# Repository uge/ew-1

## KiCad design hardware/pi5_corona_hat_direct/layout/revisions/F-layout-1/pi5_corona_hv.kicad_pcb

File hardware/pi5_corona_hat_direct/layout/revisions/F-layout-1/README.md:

# Initial four-layer PCB placement

Open `../pi5_corona_hv.kicad_pro` and its PCB editor. The board is saved in KiCad 10 format. All 152 schematic footprints, net assignments, procurement fields and native schematic paths are imported. C63 and R64 remain DNP. Seven board-only mounting holes are added.

The main carrier is **340 × 180 mm**. The optical daughterboard is **30 × 20 mm**, connected by a **12 × 5 mm** break-off neck, for an overall **340 × 205 mm** envelope. These dimensions are an initial accommodation of the large through-hole multiplier parts and linear resistor strings, subject to enclosure and clearance review.

The upper-left 65 × 56 mm reference envelope contains the Pi interface. Four mounting holes use a 58 × 49 mm pitch. J2 is on B.Cu to mate with the Pi header: pad 1 at (58.37, 54.77), pad 2 at (58.37, 52.23), and pad 40 at (106.63, 52.23) mm. The mounting-hole drill is nominally 2.7 mm. Review mechanical tolerances and the Pi 5 cooler, cables and enclosure. This extended carrier is not a standard HAT outline or a claim of HAT certification. Mechanical reference: https://github.com/raspberrypi/hats/blob/master/hat-board-mechanical.pdf.

| Layer | Intended use |
|---|---|
| F.Cu | Components, short critical connections and HV routing |
| In1.Cu | Filled logic GND plane limited to the low-voltage area |
| In2.Cu | Reserved for local low-voltage power distribution |
| B.Cu | Pi socket and additional signal routing |

Nominal board thickness is 1.6 mm. Manufacturer dielectric thicknesses and copper weights remain to be selected. Internal-layer rule areas prohibit tracks, vias and fills under the transformer and HV area, starting at x = 122 mm. Through-hole annuli are permitted. GND is not poured beneath the HV ladder, ballast or divider. HV_RETURN remains a separate schematic net. These restrictions do not establish a verified creepage or voltage rating.

USB-C, PD negotiation, the eFuse and bulk capacitance form a distinct placement group. Bridge decoupling and recirculation clamps are near U2, and T1 bridges toward the multiplier. Six multiplier columns have paired capacitors, diodes and three-resistor bleeders. The ballast and divider are linear strings; the divider progresses back toward U4. U8, J51, C80 and C81 are on the optical mini-board; J50 is on the main board. Only GND, 3V3, SDA and SCL may eventually cross its break-off neck. Neck traces and the mechanical cutting process are not yet implemented.

## Validation and remaining work

The final checks report **zero schematic parity issues**, matching net assignments for every schematic pin, and no courtyard overlaps. The initial routing pass has **285 unconnected-item reports**. One DRC warning documents the D3 instance's silkscreen adjustment: its silk was moved to F.Fab to avoid pad overlap, so it differs from the library copy. The DRC report is retained in `../exports/initial-pcb-drc.json`; validation is in `../exports/initial-pcb-validation.json`.

Before routing/release, resolve the existing J60 termination rating, relay supply/interlock review and transformer footprint verification. Replace the J60 placeholder with a rated termination and rework its local placement. Complete routing, establish HV clearance/creepage rules and any isolation slots, review leakage around the divider, and validate transformer/bridge thermal and current paths. Do not fabricate this placement study.

Review drawings: `../exports/initial-pcb-layout.pdf`, `.svg` and `.png`. No fabrication package or production pick-and-place file is emitted.

`create_initial_board.py` uses the KiCad 10 pcbnew PCB API and `schematic-connectivity.json`. It does not generate schematics. Re-running it overwrites the PCB with the initial placement and discards subsequent routing, so use it only deliberately. The connectivity snapshot corresponds to schematic revision F and must be refreshed after schematic changes.

## DNP Raspberry Pi 5 mechanical model

**MP1** is a locked, padless board-only footprint, explicitly DNP and excluded from BOM and placement files. It uses the official Raspberry Pi 5 STEP model from [Raspberry Pi's product portal](https://pip.raspberrypi.com/categories/892-raspberry-pi-5), stored locally with the supplied MIT license in `ionic_thrust_hv.3dshapes`. It is not an electrically connected or assembled HAT component. The footprint is on F.Cu solely to retain the native model orientation; its model is translated beneath the carrier.

The native model's PCB spans x = 0–85 and y = 0–56 mm. Its upper PCB face is at z = 1.306 mm. MP1's board anchor is (50,106) mm, with model scale 1, rotation 0 and offset (0,0,-14.906) mm. This places the Pi PCB upper face **12 mm below the carrier underside**, assuming the carrier's 1.6 mm thickness. This height is a fit-check assumption, not a validated connector mating specification.

The official header pins are centered at y = 51.23 and 53.77 mm in native CAD coordinates. Comparing these with the PCB exposed a 1.27 mm GPIO row offset; J2 was moved by -1.27 mm in board Y. All 40 pin coordinates now match the model's grid, and the four Pi mounting locations align. The existing schematic connections and connector selection are preserved.

**The extended carrier collides with the tall Pi connectors at the assumed 12 mm spacing.** The model reaches z = 17.526 mm, or 16.220 mm above the Pi PCB upper face. Geometric clearance requires more than 16.22 mm standoff spacing plus a mechanical margin, or carrier cut-outs. A taller stack also requires an appropriate GPIO extender; do not assume J2 alone provides that height. A cooler, cables and enclosure are not included in this model and need separate checks.

In KiCad's 3D Viewer, enable **Show DNP footprints** to display MP1. STEP export includes it unless `--no-dnp` is passed. The saved PCB remains DNP; the bottom-view preview was rendered from a temporary display copy with MP1 visible. See `../exports/pi5-mechanical-bottom.png` and `../exports/pi5-mechanical-validation.json`. `add_pi5_mechanical.py` updates only MP1 and the corrected J2 XY location without rebuilding the PCB or discarding routing. The initial-board script also restores MP1 when deliberately rebuilding.

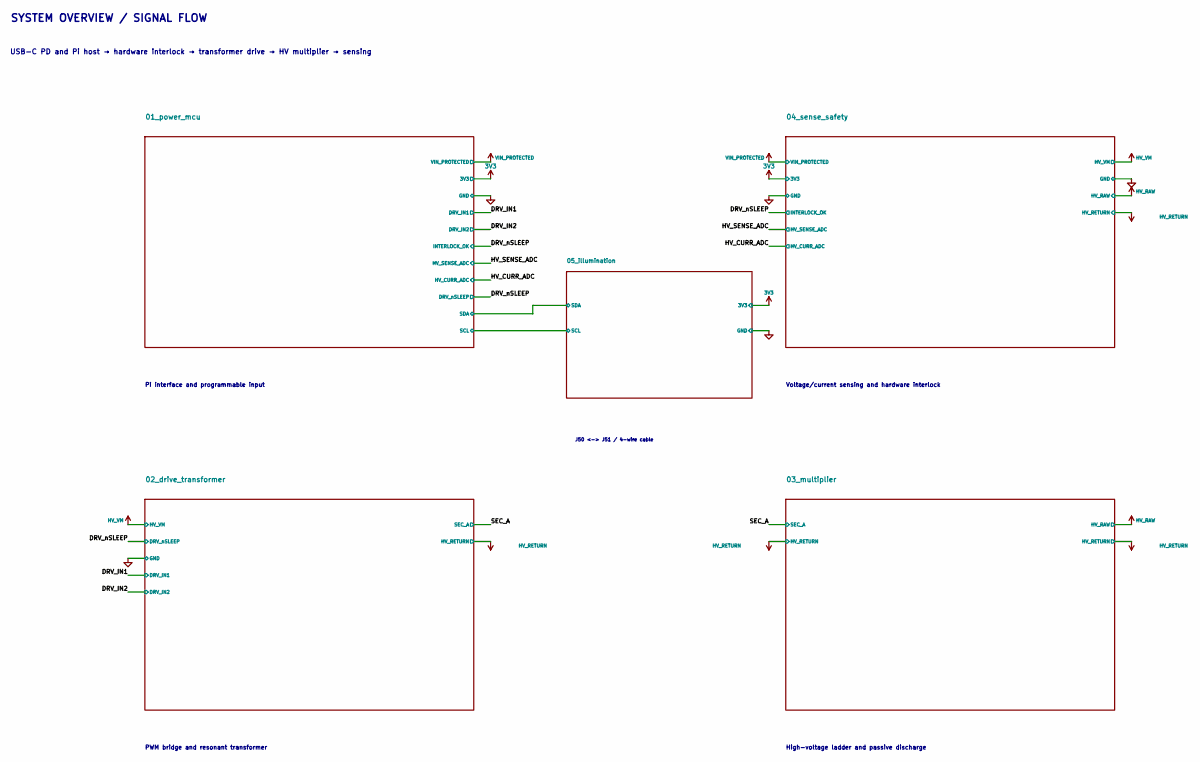
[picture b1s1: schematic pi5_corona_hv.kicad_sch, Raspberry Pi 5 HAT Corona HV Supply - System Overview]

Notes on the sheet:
SYSTEM OVERVIEW / SIGNAL FLOW
USB-C PD and Pi host → hardware interlock → transformer drive → HV multiplier → sensing
Pi interface and programmable input
Voltage/current sensing and hardware interlock
PWM bridge and resonant transformer
High-voltage ladder and passive discharge
J50 <-> J51 / 4-wire cable

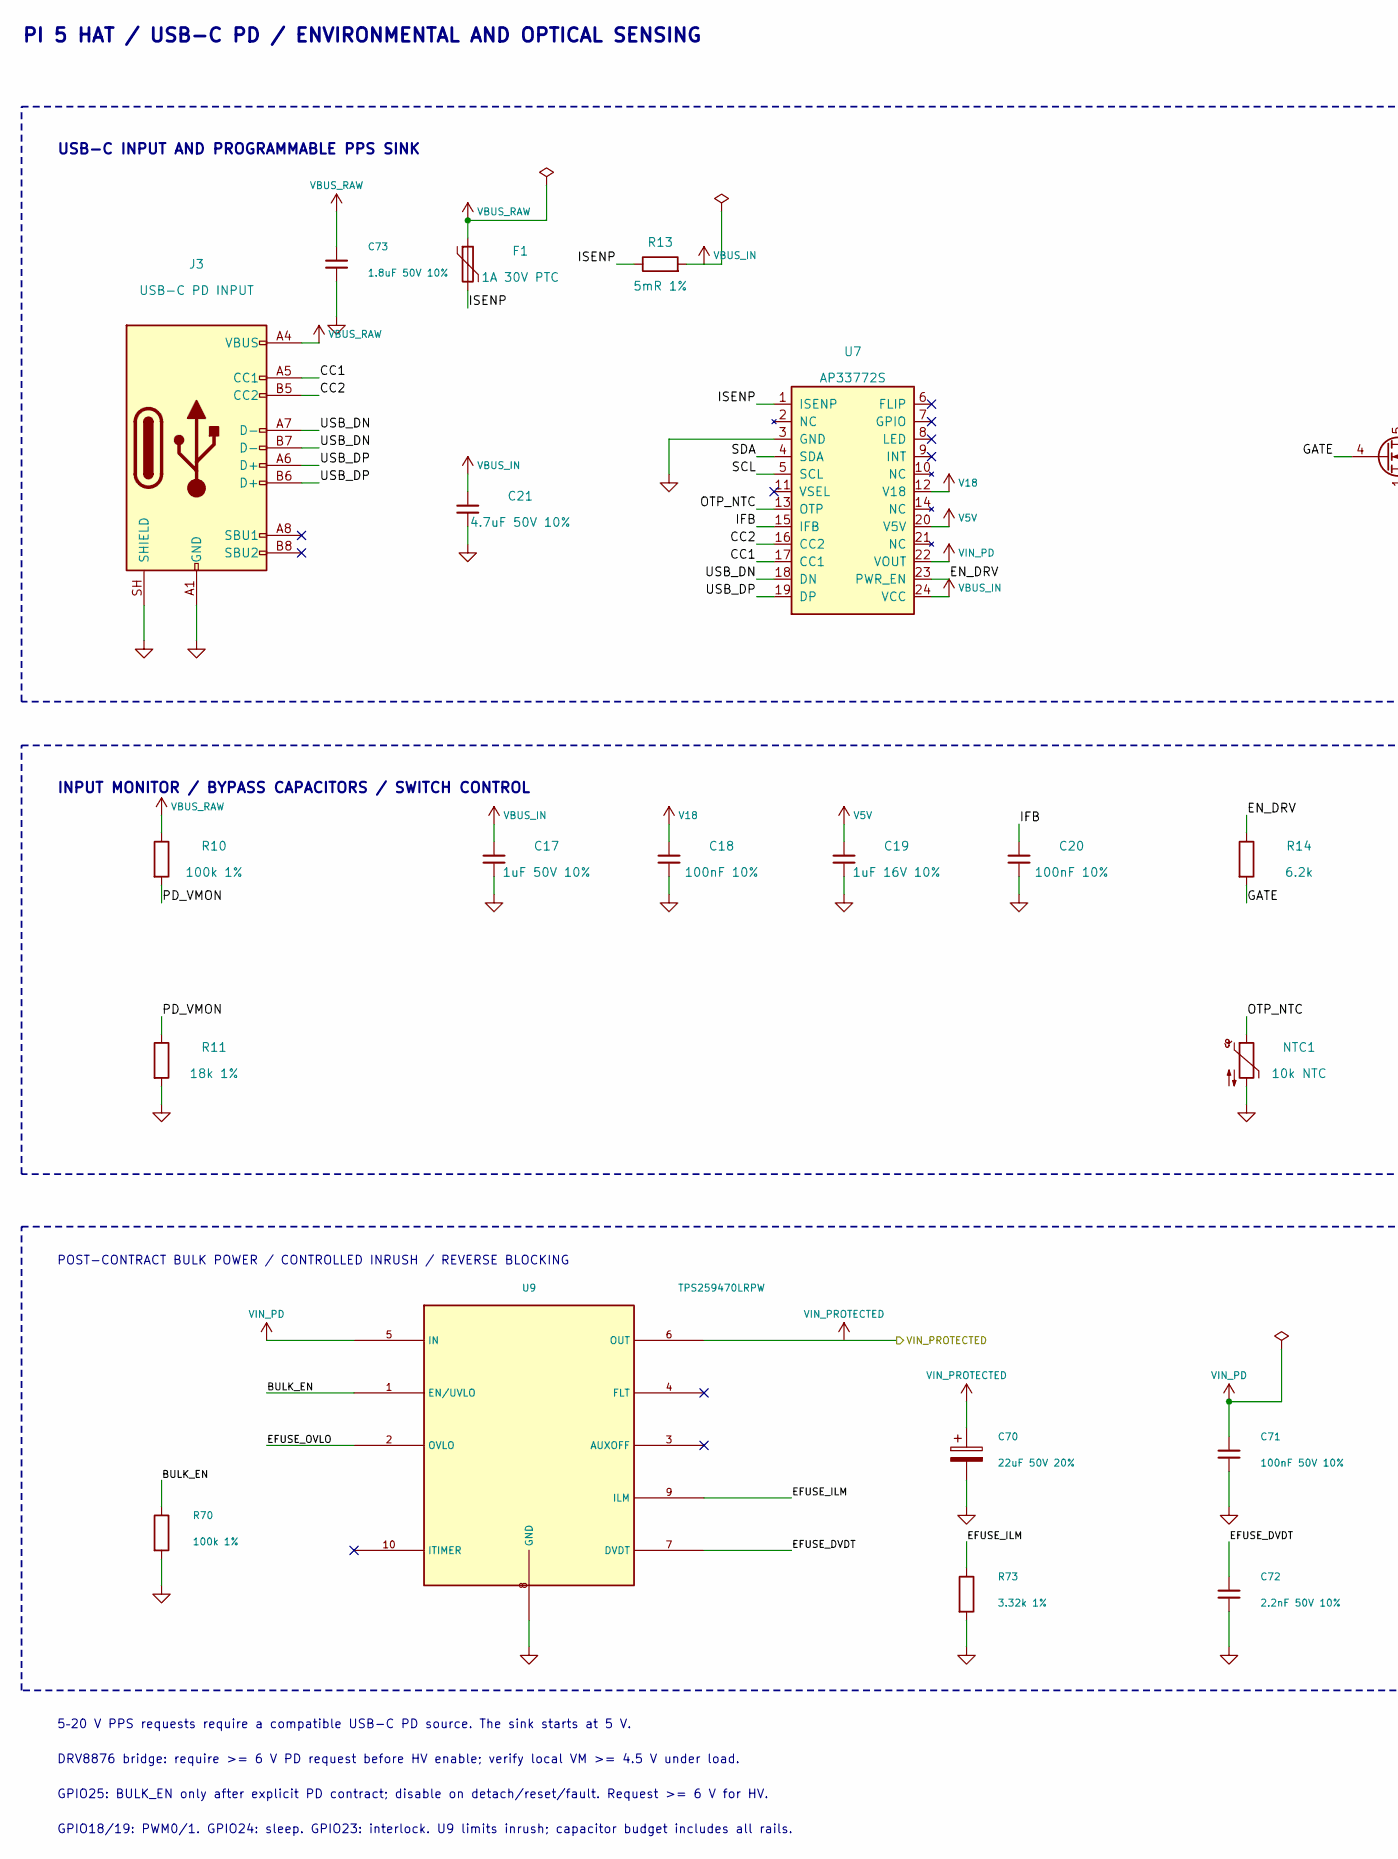
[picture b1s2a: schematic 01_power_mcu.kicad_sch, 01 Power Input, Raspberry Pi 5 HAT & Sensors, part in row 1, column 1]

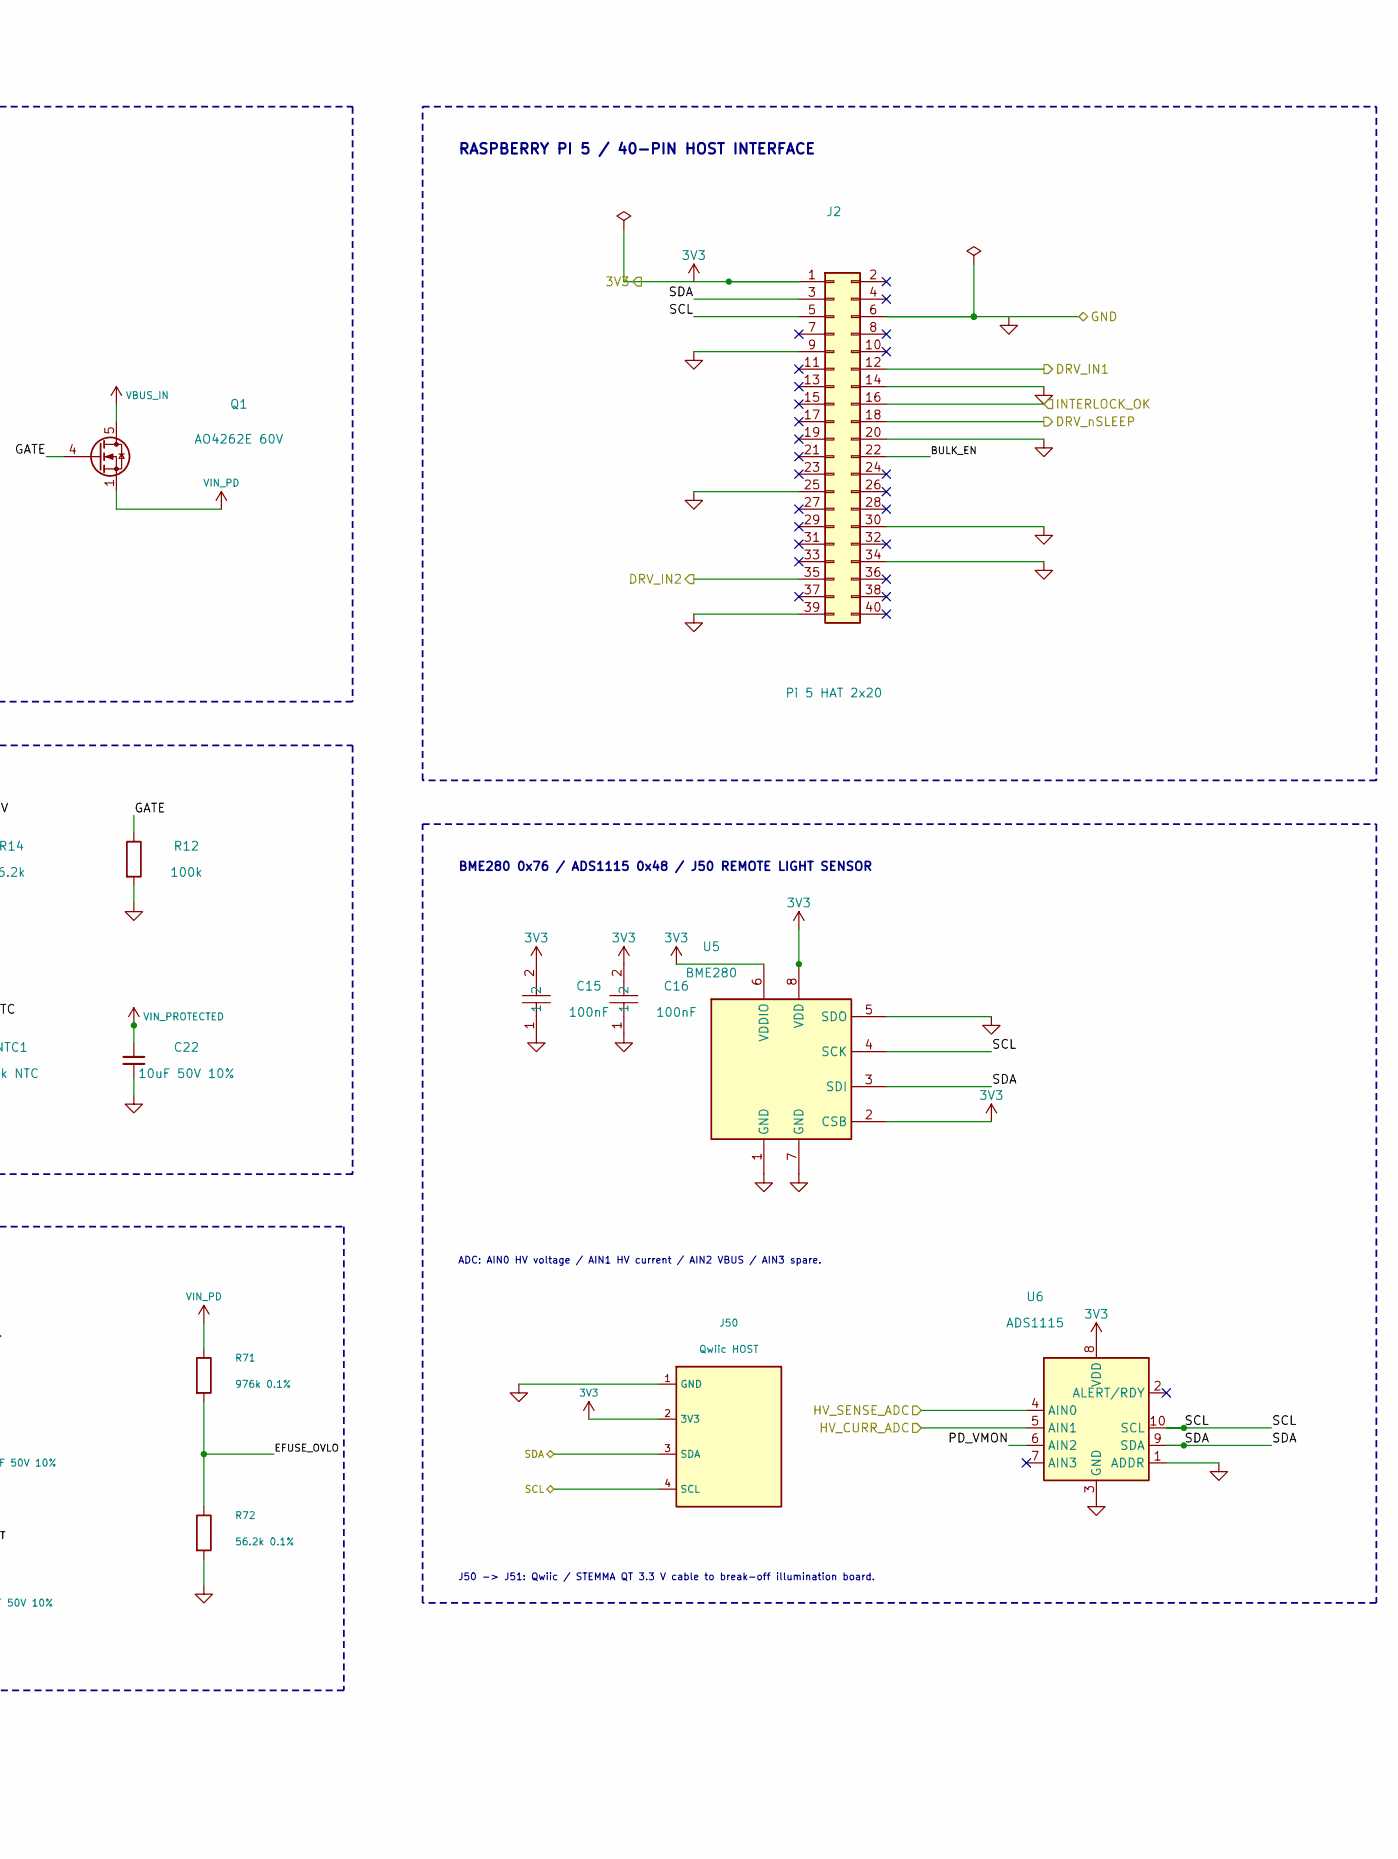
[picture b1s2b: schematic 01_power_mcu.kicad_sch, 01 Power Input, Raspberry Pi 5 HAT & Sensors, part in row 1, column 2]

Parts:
C15, C16: 100nF; C0603; MPN CC0603KRX7R9BB104; LCSC C14663
C17: 1uF 50V 10%; C_0603_1608Metric; MPN CL10B105KB8NQNC; LCSC C5199872
C18, C20: 100nF 10%; C_0603_1608Metric; MPN CC0603KRX7R9BB104; LCSC C14663
C19: 1uF 16V 10%; C_0603_1608Metric; MPN CL10B105KB8NQNC; LCSC C5199872
C21: 4.7uF 50V 10%; C_1210_3225Metric; MPN GCM32ER71H475KA55L; LCSC C126618
C22: 10uF 50V 10%; C_1210_3225Metric; MPN UMK325AB7106KMHP; LCSC C386166
C70: 22uF 50V 20%; CP_Radial_D5.0mm_P2.00mm; MPN 50YXF22MEFC5X11; LCSC C88755
C71: 100nF 50V 10%; C_0603_1608Metric; MPN CC0603KRX7R9BB104; LCSC C14663
C72: 2.2nF 50V 10%; C_0603_1608Metric; MPN 0603B222K500NT; LCSC C1604
C73: 1.8uF 50V 10%; C_2220_5750Metric; MPN C2220C185J5RAC7800; LCSC C3900748
F1: 1A 30V PTC; Fuse_1206_3216Metric; MPN BSMD1206-100-30V; LCSC C5358568
J2: Pi 5 HAT 2x20; PinSocket_2x20_P2.54mm_Vertical; MPN 2.54-2*20; LCSC C2977589
J3: USB-C PD INPUT; USB_C_Receptacle_HCTL_HC-TYPE-C-16P-01A; MPN HC-TYPE-C-16P-01A; LCSC C2894897
J50: Qwiic HOST; JST_SH_SM04B-SRSS-TB_1x04-1MP_P1.00mm_Horizontal; MPN SM04B-SRSS-TB(LF)(SN); LCSC C160404
NTC1: 10k NTC; R_0603_1608Metric; MPN NCP18XH103F03RB; LCSC C13564
Q1: AO4262E 60V; SO-8_3.9x4.9mm_P1.27mm; MPN AO4262E; LCSC C431178
R10, R70: 100k 1%; R_0603_1608Metric; MPN 0603WAF1003T5E; LCSC C25803
R11: 18k 1%; R_0603_1608Metric; MPN 0603WAF1802T5E; LCSC C25810
R12: 100k; R_0603_1608Metric; MPN 0603WAF1003T5E; LCSC C25803
R13: 5mR 1%; R_2512_6332Metric; MPN RLP25FEGMR005; LCSC C393074
R14: 6.2k; R_0603_1608Metric; MPN 0603WAF6201T5E; LCSC C4260
R71: 976k 0.1%; R_0805_2012Metric; MPN RT0805BRD07976KL; LCSC C865713
R72: 56.2k 0.1%; R_0603_1608Metric; MPN RT0603BRD0756K2L; LCSC C705784
R73: 3.32k 1%; R_0603_1608Metric; MPN RT0603FRD073K32L; LCSC C863430
U5: BME280; Bosch_LGA-8_2.5x2.5mm_P0.65mm_ClockwisePinNumbering; MPN BME280; LCSC C92489
U6: ADS1115; TSSOP-10_3x3mm_P0.5mm; MPN ADS1115IDGSR; LCSC C37593
U7: AP33772S; QFN-24-1EP_4x4mm_P0.5mm_EP2.7x2.7mm; MPN AP33772SDKZ-13-FA01; LCSC C24374260
U9: TPS259470LRPW; Texas_RPW0010A_VQFN-HR-10_2x2mm; MPN TPS259470LRPWR; LCSC C3662793

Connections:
3V3: C15.2, C16.2, J2.1, J50.2 (3V3), U5.2 (CSB), U5.6 (VDDIO), U5.8 (VDD), U6.8 (VDD); also elsewhere on the board
/01_power_mcu/BULK_EN: J2.22, R70.1, U9.1 (EN/UVLO)
/01_power_mcu/CC1: J3.A5 (CC1), U7.17 (CC1)
/01_power_mcu/CC2: J3.B5 (CC2), U7.16 (CC2)
/01_power_mcu/EFUSE_DVDT: C72.1, U9.7 (DVDT)
/01_power_mcu/EFUSE_ILM: R73.1, U9.9 (ILM)
/01_power_mcu/EFUSE_OVLO: R71.2, R72.1, U9.2 (OVLO)
/01_power_mcu/EN_DRV: R14.1, U7.23 (PWR_EN)
/01_power_mcu/GATE: Q1.4 (G), R12.1, R14.2
/01_power_mcu/IFB: C20.1, U7.15 (IFB)
/01_power_mcu/ISENP: F1.2, R13.1, U7.1 (ISENP)
/01_power_mcu/OTP_NTC: NTC1.1, U7.13 (OTP)
/01_power_mcu/PD_VMON: R10.2, R11.1, U6.6 (AIN2)
/01_power_mcu/SCL: J2.5, J50.4 (SCL), U5.4 (SCK), U6.10 (SCL), U7.5 (SCL); also elsewhere on the board
/01_power_mcu/SDA: J2.3, J50.3 (SDA), U5.3 (SDI), U6.9 (SDA), U7.4 (SDA); also elsewhere on the board
/01_power_mcu/USB_DN: J3.A7 (D-), J3.B7 (D-), U7.18 (DN)
/01_power_mcu/USB_DP: J3.A6 (D+), J3.B6 (D+), U7.19 (DP)
/01_power_mcu/V5V: C19.1, U7.20 (V5V)
/01_power_mcu/V18: C18.1, U7.12 (V18)
/01_power_mcu/VBUS_IN: C17.1, C21.1, Q1.5 (D), Q1.6 (D), Q1.7 (D), Q1.8 (D), R13.2, U7.24 (VCC)
/01_power_mcu/VBUS_RAW: C73.1, F1.1, J3.A4 (VBUS), J3.A9 (VBUS), J3.B4 (VBUS), J3.B9 (VBUS), R10.1
/01_power_mcu/VIN_PD: C71.1, Q1.1 (S), Q1.2 (S), Q1.3 (S), R71.1, U7.22 (VOUT), U9.5 (IN)
/DRV_IN1: J2.12; also elsewhere on the board
/DRV_IN2: J2.35; also elsewhere on the board
/DRV_nSLEEP: J2.16, J2.18; also elsewhere on the board
/HV_CURR_ADC: U6.5 (AIN1); also elsewhere on the board
/HV_SENSE_ADC: U6.4 (AIN0); also elsewhere on the board
/VIN_PROTECTED: C22.1, C70.1, U9.6 (OUT); also elsewhere on the board
GND: C15.1, C16.1, C17.2, C18.2, C19.2, C20.2, C21.2, C22.2, C70.2, C71.2, C72.2, C73.2, J2.6, J2.9, J2.14, J2.20, J2.25, J2.30, J2.34, J2.39, J3.A1 (GND), J3.A12 (GND), J3.B1 (GND), J3.B12 (GND), J3.SH (SHIELD), J50.1 (GND), NTC1.2, R11.2, R12.2, R70.2, R72.2, R73.2, U5.1 (GND), U5.5 (SDO), U5.7 (GND), U6.1 (ADDR), U6.3 (GND), U7.3 (GND), U7.25 (GND), U9.8 (GND); also elsewhere on the board

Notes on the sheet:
PI 5 HAT / USB-C PD / ENVIRONMENTAL AND OPTICAL SENSING
USB-C INPUT AND PROGRAMMABLE PPS SINK
INPUT MONITOR / BYPASS CAPACITORS / SWITCH CONTROL
RASPBERRY PI 5 / 40-PIN HOST INTERFACE
BME280 0x76 / ADS1115 0x48 / J50 REMOTE LIGHT SENSOR
5–20 V PPS requests require a compatible USB-C PD source. The sink starts at 5 V.
DRV8876 bridge: require >= 6 V PD request before HV enable; verify local VM >= 4.5 V under load.
GPIO25: BULK_EN only after explicit PD contract; disable on detach/reset/fault. Request >= 6 V for HV.
GPIO18/19: PWM0/1. GPIO24: sleep. GPIO23: interlock. U9 limits inrush; capacitor budget includes all rails.
ADC: AIN0 HV voltage / AIN1 HV current / AIN2 VBUS / AIN3 spare.
J50 -> J51: Qwiic / STEMMA QT 3.3 V cable to break-off illumination board.
POST-CONTRACT BULK POWER / CONTROLLED INRUSH / REVERSE BLOCKING

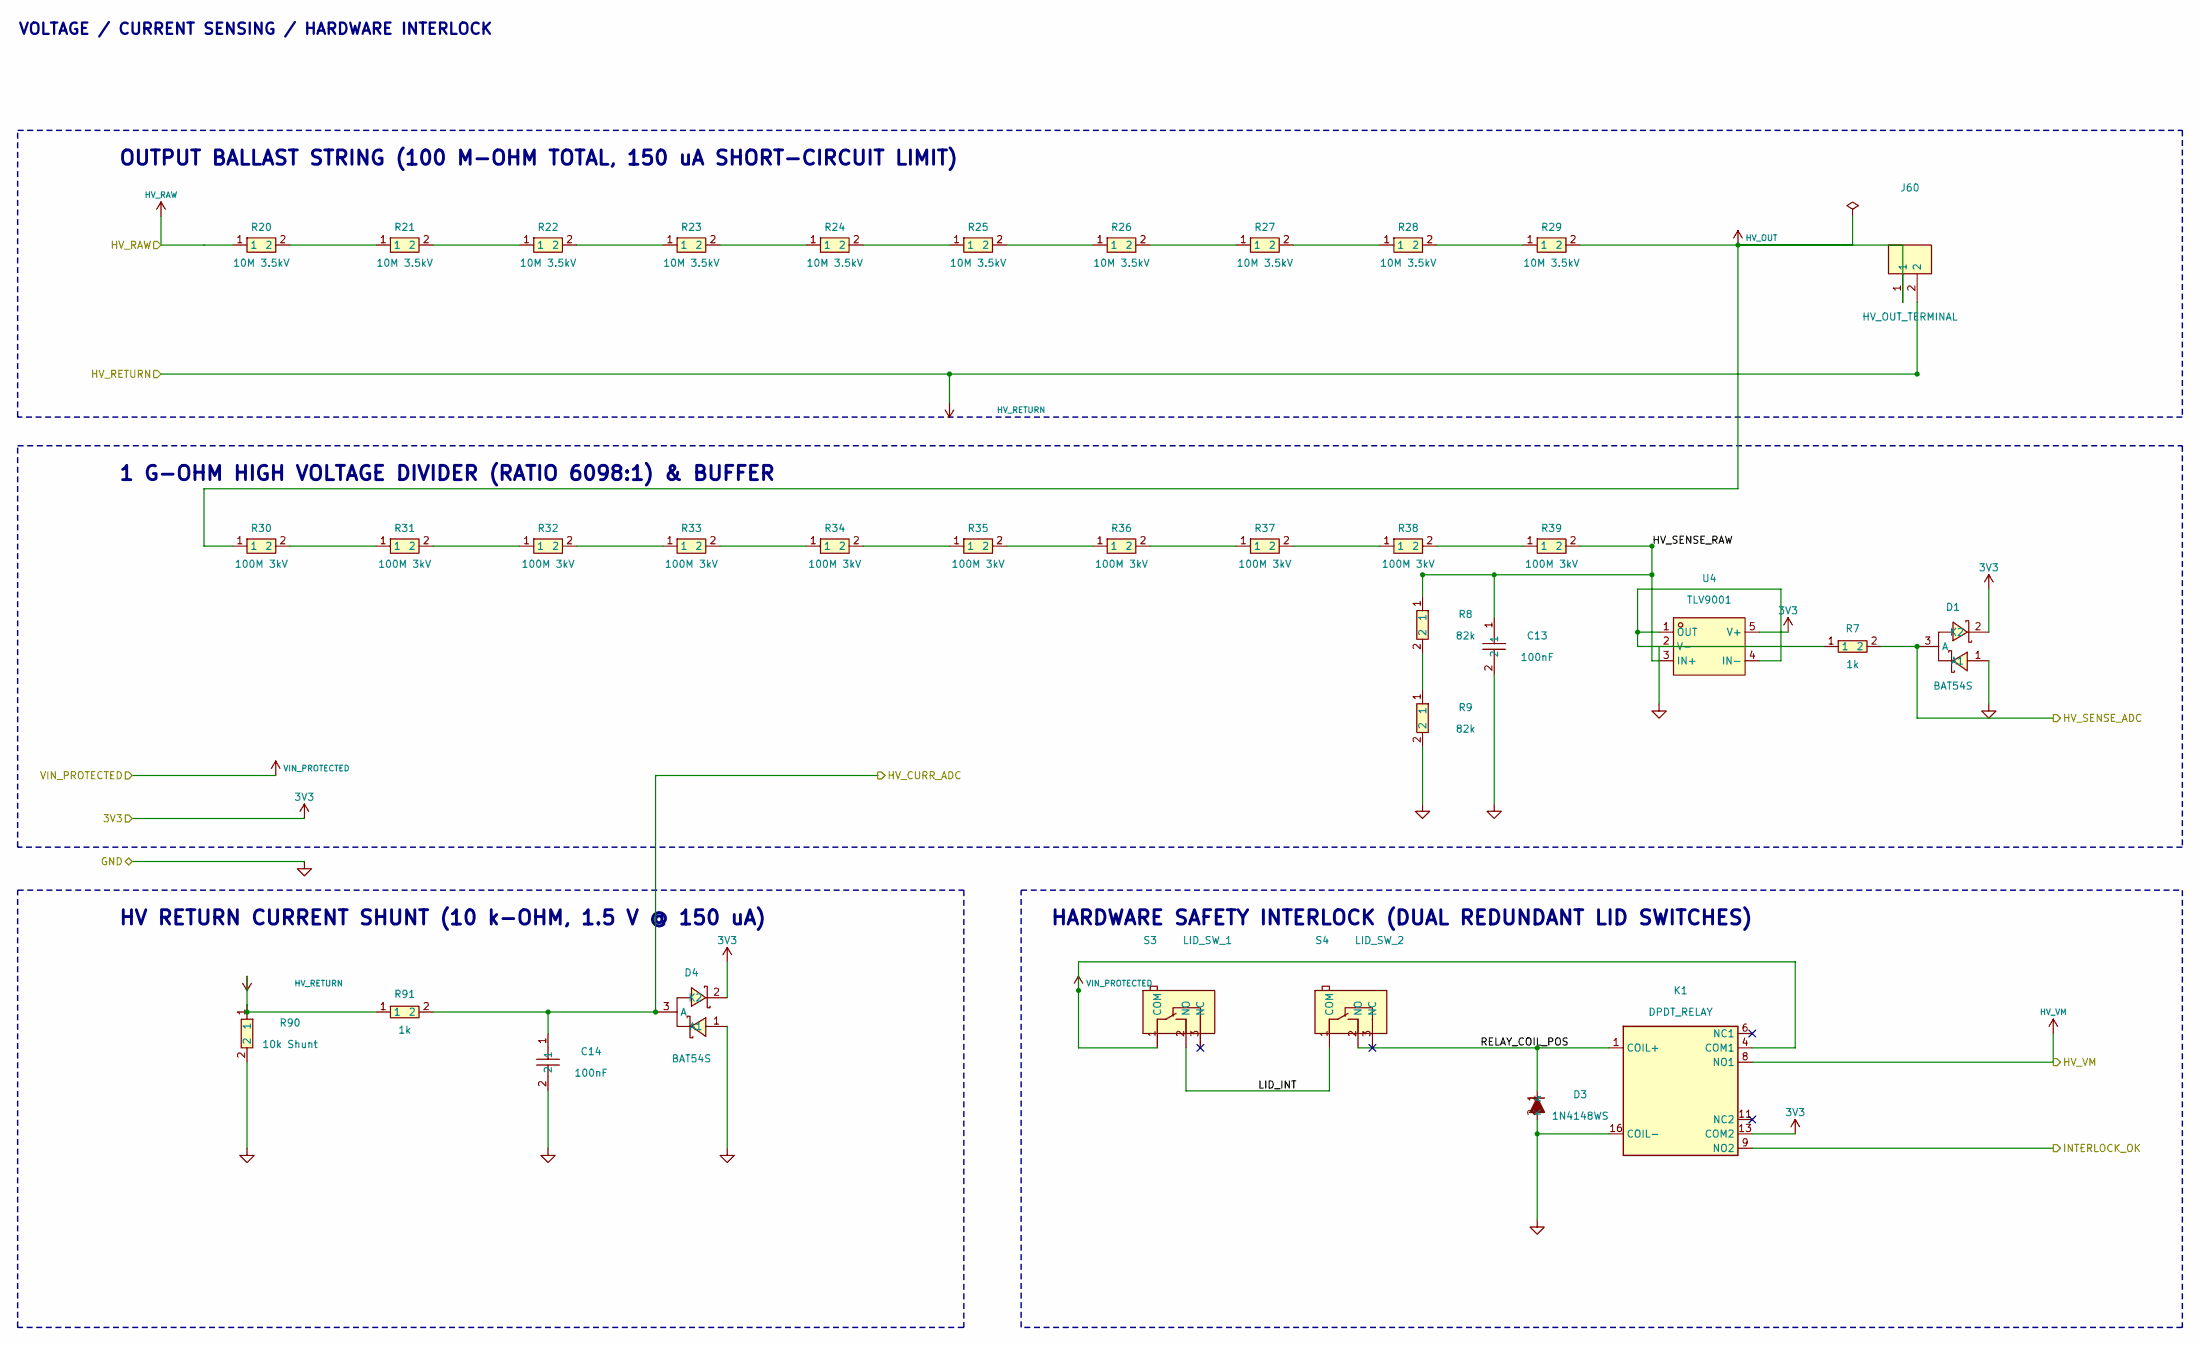
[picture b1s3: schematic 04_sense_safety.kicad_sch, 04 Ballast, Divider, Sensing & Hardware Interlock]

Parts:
C13, C14: 100nF; C0603; MPN CC0603KRX7R9BB104; LCSC Part C14663
D1, D4: BAT54S; SOT-23-3_L2.9-W1.3-P1.90-LS2.4-BR; MPN BAT54S; LCSC Part C83935
D3: 1N4148WS; D_SOD-323; MPN 1N4148WS; LCSC Part C2128
J60: HV_OUT_TERMINAL; CONN-TH_2P-P5.00_WJ500V-5.08-2P; JLCPCB Library Unknown
K1: DPDT_RELAY; Relay_DPDT_N4078; MPN N4078-2C-DC12V-0.2W; LCSC Part C52195125
R7, R91: 1k; R0603; MPN 0603WAF1001T5E; LCSC Part C21190
R8, R9: 82k; R0603; MPN 0603WAF8202T5E; LCSC Part C23254
R20, R21, R22, R23, R24, R25, R26, R27, R28, R29: 10M 3.5kV; RES-TH_BD3.5-L9.5-P13.50-D0.6; MPN MGR0W2J0106A10; LCSC Part C51904770
R30, R31, R32, R33, R34, R35, R36, R37, R38, R39: 100M 3kV; R_2512_6332Metric; MPN CHV2512-JW-107ELF; LCSC Part C2089706
R90: 10k Shunt; R0603; MPN 0603WAF1002T5E; LCSC Part C25804
S3: LID_SW_1; SW-TH_D2F-L; MPN D2F-L; LCSC Part C231337
S4: LID_SW_2; SW-TH_D2F-L; MPN D2F-L; LCSC Part C231337
U4: TLV9001; SOT-23-5_L3.0-W1.7-P0.95-LS2.8-BR; MPN TLV9001IDBVR; LCSC Part C398363

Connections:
3V3: D1.2 (K2), D4.2 (K2), K1.13 (COM2), U4.5 (V+); also elsewhere on the board
/04_sense_safety/HV_OUT: J60.1, R29.2, R30.1
/04_sense_safety/HV_SENSE_RAW: C13.1, R8.1, R39.2, U4.3 (IN+)
/04_sense_safety/LID_INT: S3.2 (NO), S4.1 (COM)
/04_sense_safety/RELAY_COIL_POS: D3.1 (K), K1.1 (COIL+), S4.2 (NO)
/DRV_nSLEEP: K1.9 (NO2); also elsewhere on the board
/HV_CURR_ADC: C14.1, D4.3 (A), R91.2; also elsewhere on the board
/HV_RAW: R20.1; also elsewhere on the board
/HV_RETURN: J60.2, R90.1, R91.1; also elsewhere on the board
/HV_SENSE_ADC: D1.3 (A), R7.2; also elsewhere on the board
/HV_VM: K1.8 (NO1); also elsewhere on the board
/VIN_PROTECTED: K1.4 (COM1), S3.1 (COM); also elsewhere on the board
GND: C13.2, C14.2, D1.1 (A1), D3.2 (A), D4.1 (A1), K1.16 (COIL-), R9.2, R90.2, U4.2 (V-); also elsewhere on the board
unnamed: R8.2, R9.1
unnamed: R20.2, R21.1
unnamed: R21.2, R22.1
unnamed: R22.2, R23.1
unnamed: R23.2, R24.1
unnamed: R24.2, R25.1
unnamed: R25.2, R26.1
unnamed: R26.2, R27.1
unnamed: R27.2, R28.1
unnamed: R28.2, R29.1
unnamed: R30.2, R31.1
unnamed: R31.2, R32.1
unnamed: R32.2, R33.1
unnamed: R33.2, R34.1
unnamed: R34.2, R35.1
unnamed: R35.2, R36.1
unnamed: R36.2, R37.1
unnamed: R37.2, R38.1
unnamed: R38.2, R39.1
unnamed: R7.1, U4.1 (OUT), U4.4 (IN-)

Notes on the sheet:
OUTPUT BALLAST STRING (100 M-OHM TOTAL, 150 uA SHORT-CIRCUIT LIMIT)
1 G-OHM HIGH VOLTAGE DIVIDER (RATIO 6098:1) & BUFFER
HV RETURN CURRENT SHUNT (10 k-OHM, 1.5 V @ 150 uA)
HARDWARE SAFETY INTERLOCK (DUAL REDUNDANT LID SWITCHES)
VOLTAGE / CURRENT SENSING / HARDWARE INTERLOCK

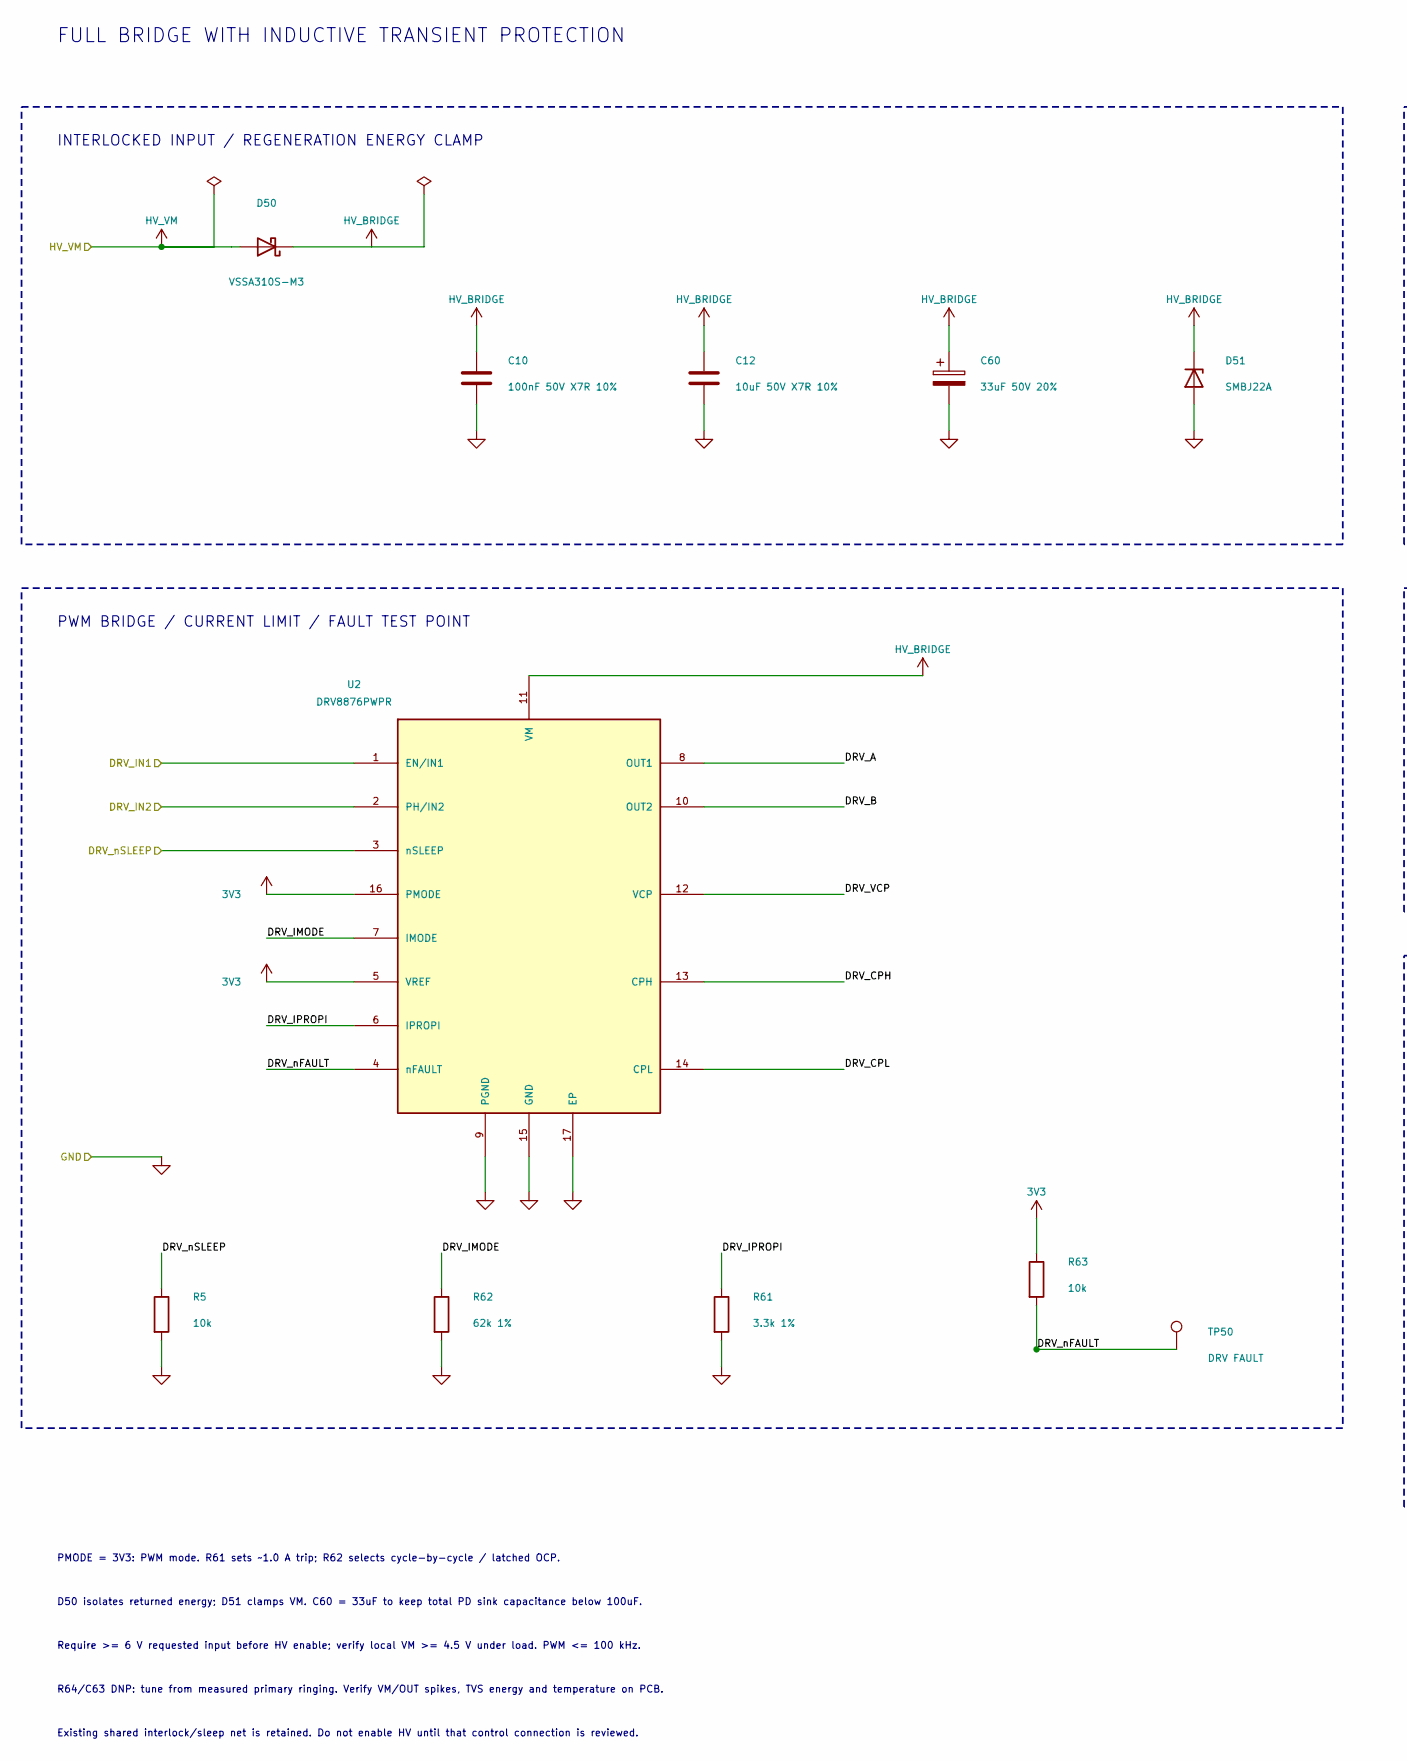
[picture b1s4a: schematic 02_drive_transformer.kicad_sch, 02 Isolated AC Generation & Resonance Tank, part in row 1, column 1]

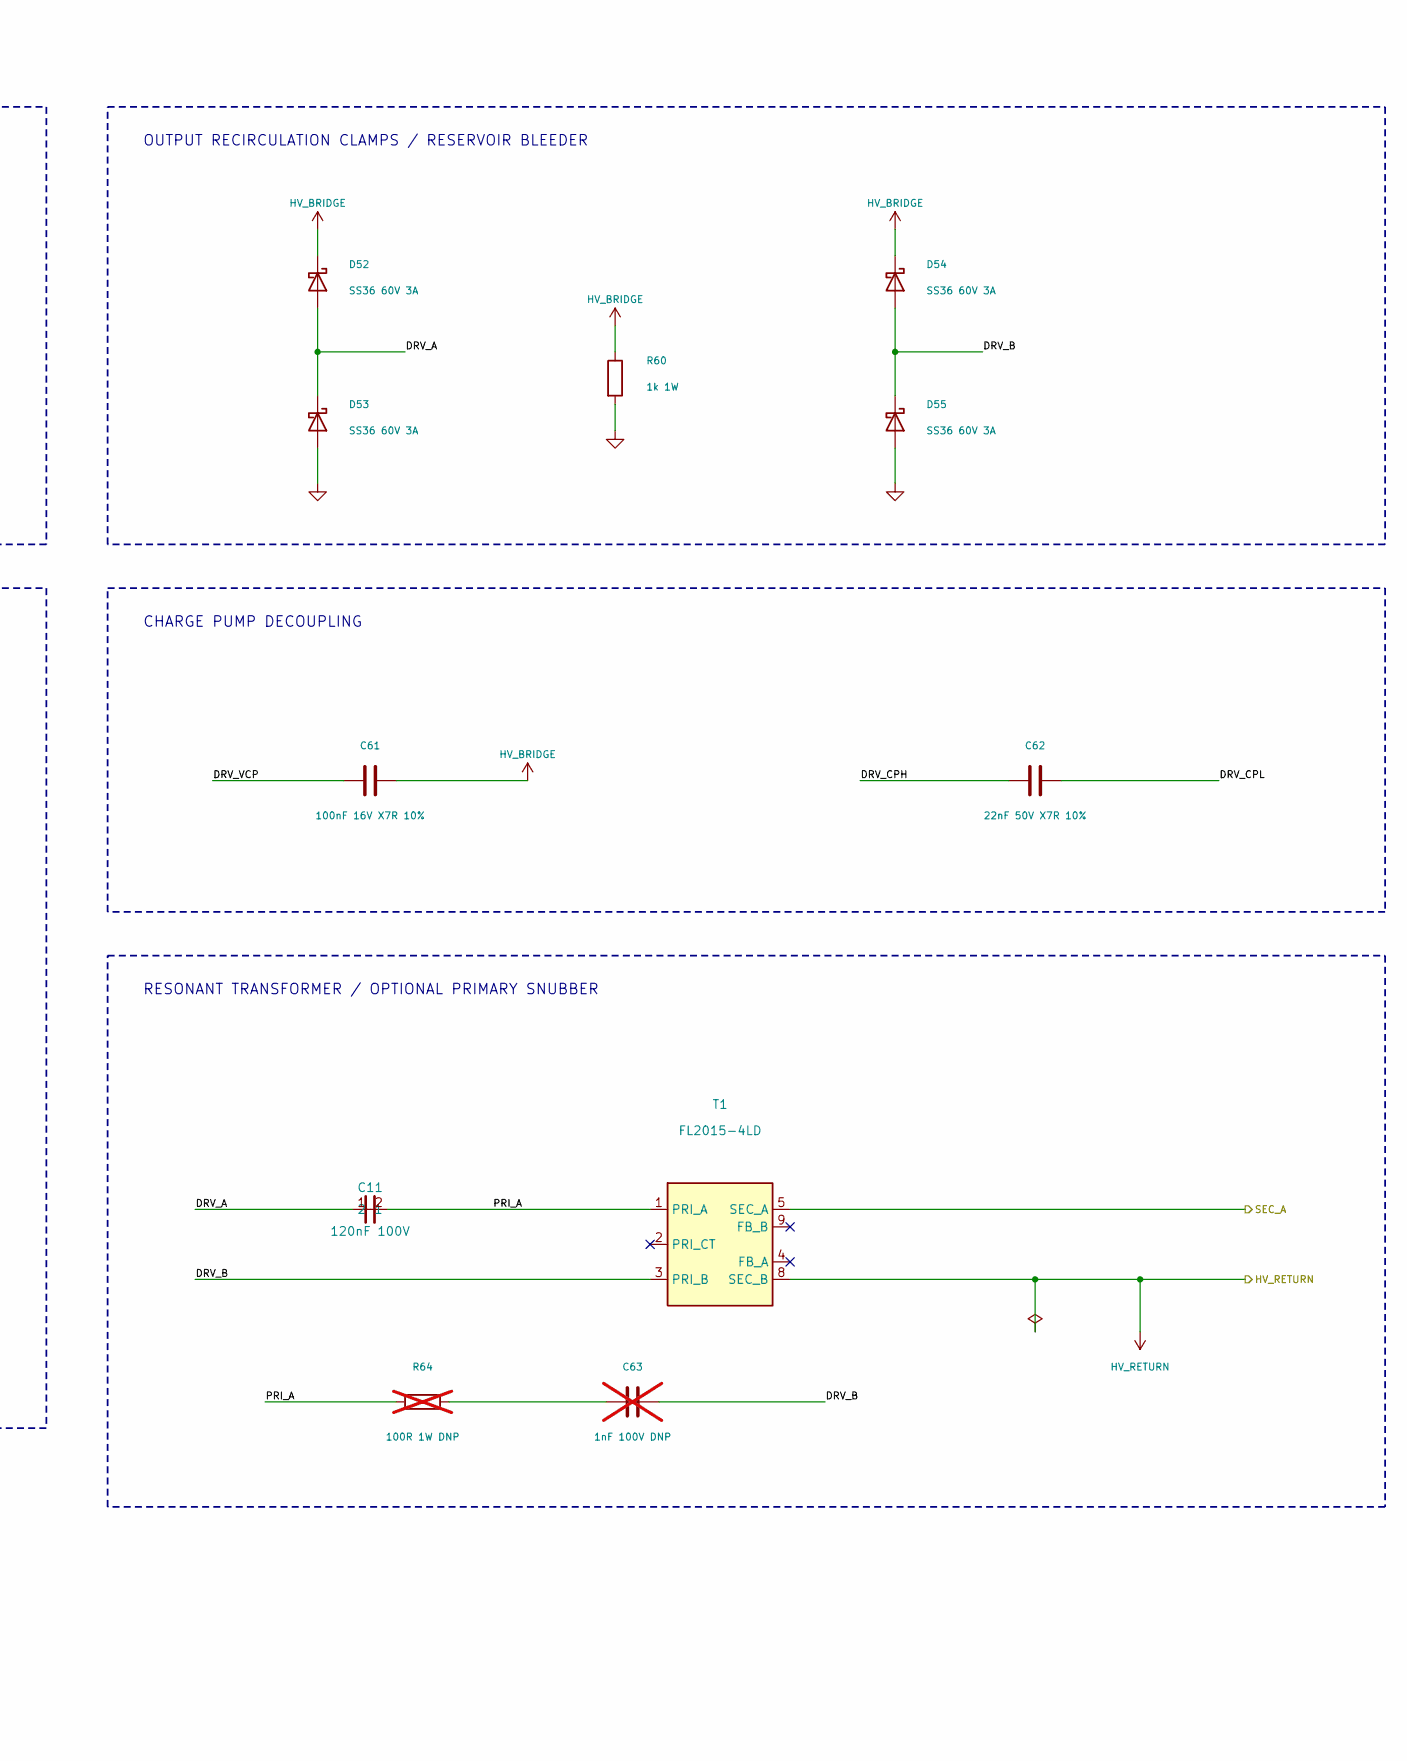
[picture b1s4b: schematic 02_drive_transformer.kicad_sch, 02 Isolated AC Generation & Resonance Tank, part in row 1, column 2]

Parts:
C10: 100nF 50V X7R 10%; C_0603_1608Metric; MPN CC0603KRX7R9BB104; LCSC C14663
C11: 120nF 100V; Film_KYET_18x10mm_P15mm; MPN MMKP124J2J1501; LCSC Part C2991056
C12: 10uF 50V X7R 10%; C_1210_3225Metric; MPN UMK325AB7106KMHP; LCSC C386166
C60: 33uF 50V 20%; CP_Radial_D5.0mm_P2.00mm; MPN 50YXJ33M5X11; LCSC C2839476
C61: 100nF 16V X7R 10%; C_0603_1608Metric; MPN CC0603KRX7R9BB104; LCSC C14663
C62: 22nF 50V X7R 10%; C_0603_1608Metric; MPN CL10B223KB8NNNC; LCSC C21122
C63: 1nF 100V DNP; C_0805_2012Metric; MPN GRM2165C2A102JA01D; LCSC C162289; not fitted
D50: VSSA310S-M3; D_SMA; MPN VSSA310S-M3/61T; LCSC C145232
D51: SMBJ22A; D_SMB; MPN SMBJ22A; LCSC C224015
D52, D53, D54, D55: SS36 60V 3A; D_SMC; MPN SS36C; LCSC C16237
R5, R63: 10k; R_0603_1608Metric; MPN 0603WAF1002T5E; LCSC C25804
R60: 1k 1W; R_2512_6332Metric; MPN 25121WF1001T4E; LCSC C54315
R61: 3.3k 1%; R_0603_1608Metric; MPN 0603WAF3301T5E; LCSC C22978
R62: 62k 1%; R_0603_1608Metric; MPN 0603WAF6202T5E; LCSC C23221
R64: 100R 1W DNP; R_2512_6332Metric; MPN 25121WF1000T4E; LCSC C35218; not fitted
T1: FL2015-4LD; Coilcraft_FL2015-4L; MPN FL2015-4LD; JLCPCB Library Unknown
TP50: DRV FAULT; TestPoint_Pad_D1.5mm; JLCPCB Library Unknown
U2: DRV8876PWPR; HTSSOP-16-1EP_4.4x5mm_P0.65mm_EP3.4x5mm_Mask3x3mm_ThermalVi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; MPN DRV8876PWPR; LCSC C575551

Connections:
3V3: R63.1, U2.5 (VREF), U2.16 (PMODE); also elsewhere on the board
/02_drive_transformer/DRV_A: C11.1, D52.2 (A), D53.1 (K), U2.8 (OUT1)
/02_drive_transformer/DRV_B: C63.2, D54.2 (A), D55.1 (K), T1.3 (PRI_B), U2.10 (OUT2)
/02_drive_transformer/DRV_CPH: C62.1, U2.13 (CPH)
/02_drive_transformer/DRV_CPL: C62.2, U2.14 (CPL)
/02_drive_transformer/DRV_IMODE: R62.1, U2.7 (IMODE)
/02_drive_transformer/DRV_IPROPI: R61.1, U2.6 (IPROPI)
/02_drive_transformer/DRV_VCP: C61.1, U2.12 (VCP)
/02_drive_transformer/DRV_nFAULT: R63.2, TP50.1, U2.4 (nFAULT)
/02_drive_transformer/HV_BRIDGE: C10.1, C12.1, C60.1, C61.2, D50.1 (K), D51.1 (K), D52.1 (K), D54.1 (K), R60.1, U2.11 (VM)
/02_drive_transformer/PRI_A: C11.2, R64.1, T1.1 (PRI_A)
/DRV_IN1: U2.1 (EN/IN1); also elsewhere on the board
/DRV_IN2: U2.2 (PH/IN2); also elsewhere on the board
/DRV_nSLEEP: R5.1, U2.3 (nSLEEP); also elsewhere on the board
/HV_RETURN: T1.8 (SEC_B); also elsewhere on the board
/HV_VM: D50.2 (A); also elsewhere on the board
/SEC_A: T1.5 (SEC_A); also elsewhere on the board
GND: C10.2, C12.2, C60.2, D51.2 (A), D53.2 (A), D55.2 (A), R5.2, R60.2, R61.2, R62.2, U2.9 (PGND), U2.15 (GND), U2.17 (EP); also elsewhere on the board
unnamed: C63.1, R64.2

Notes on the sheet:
INTERLOCKED INPUT / REGENERATION ENERGY CLAMP
OUTPUT RECIRCULATION CLAMPS / RESERVOIR BLEEDER
PWM BRIDGE / CURRENT LIMIT / FAULT TEST POINT
CHARGE PUMP DECOUPLING
RESONANT TRANSFORMER / OPTIONAL PRIMARY SNUBBER
FULL BRIDGE WITH INDUCTIVE TRANSIENT PROTECTION
PMODE = 3V3: PWM mode. R61 sets ~1.0 A trip; R62 selects cycle-by-cycle / latched OCP.
D50 isolates returned energy; D51 clamps VM. C60 = 33uF to keep total PD sink capacitance below 100uF.
Require >= 6 V requested input before HV enable; verify local VM >= 4.5 V under load. PWM <= 100 kHz.
R64/C63 DNP: tune from measured primary ringing. Verify VM/OUT spikes, TVS energy and temperature on PCB.
Existing shared interlock/sleep net is retained. Do not enable HV until that control connection is reviewed.
